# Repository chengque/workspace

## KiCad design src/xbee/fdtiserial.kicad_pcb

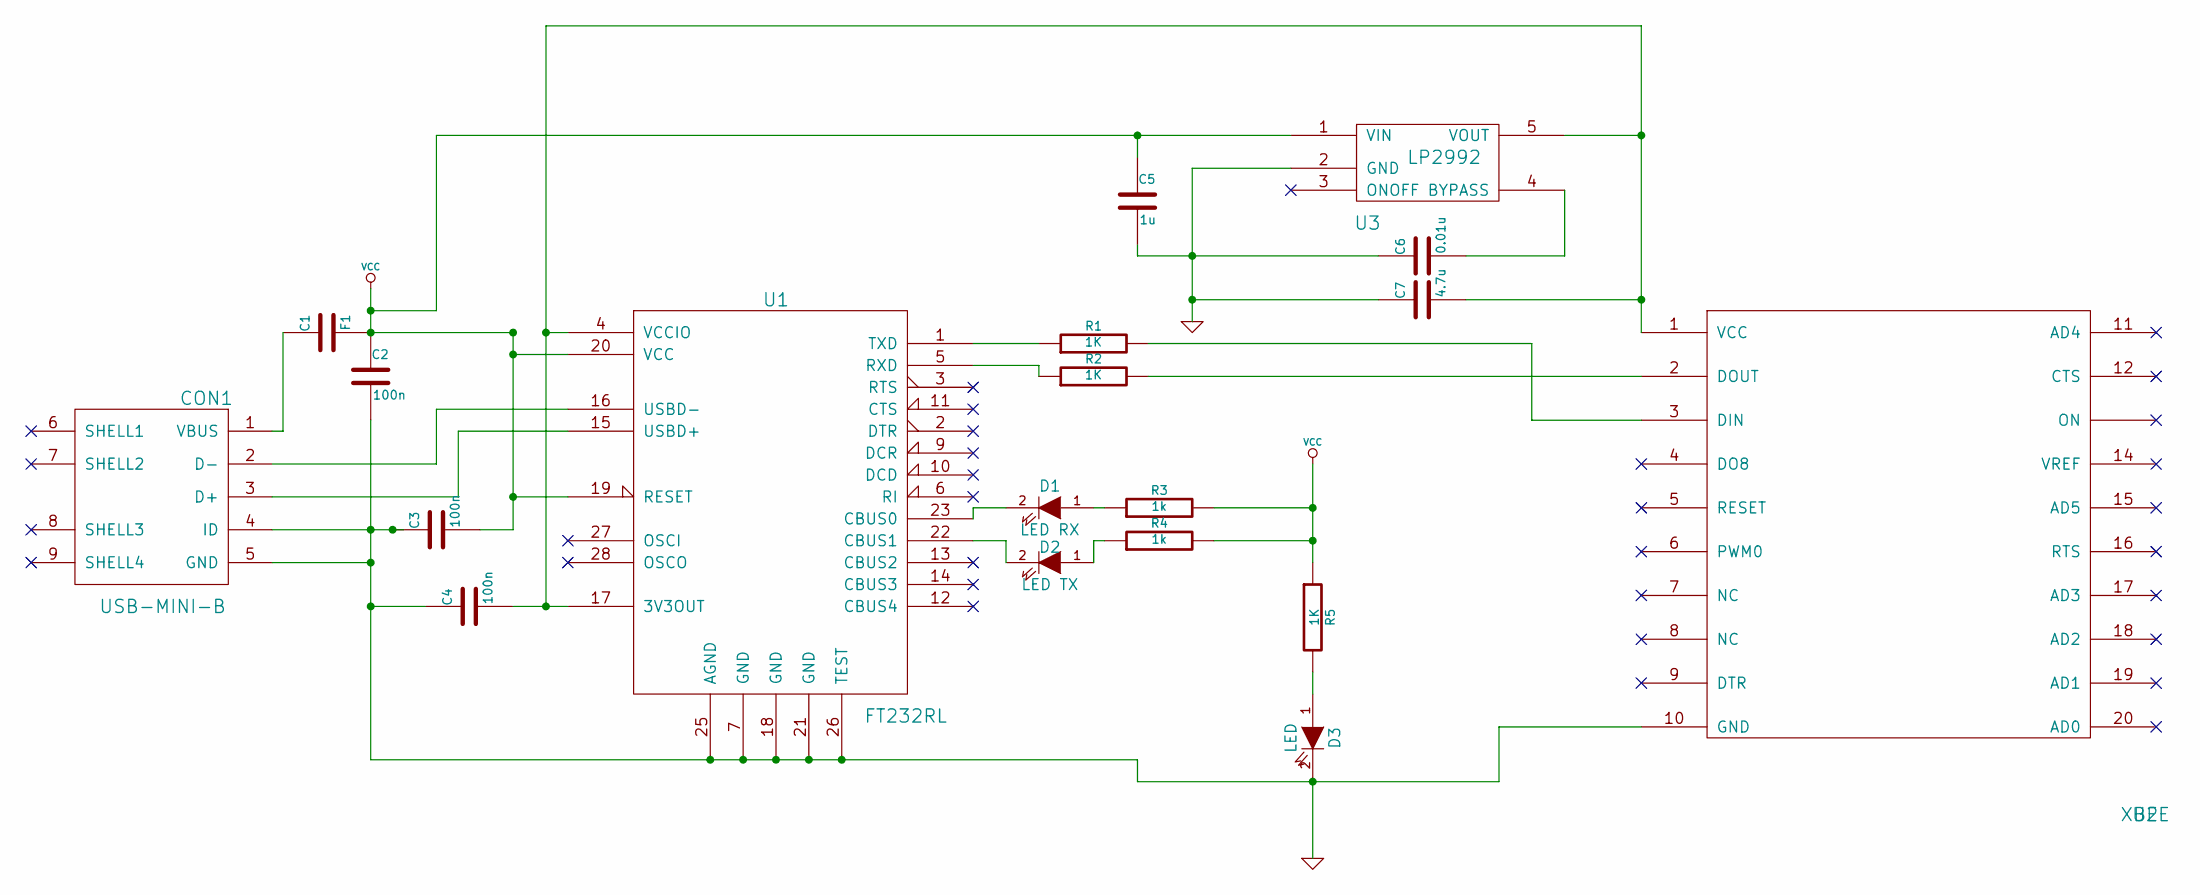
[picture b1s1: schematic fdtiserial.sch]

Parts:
C1: F1
C2, C3, C4: 100n
C5: 1u
C6: 0.01u
C7: 4.7u
CON1: USB-MINI-B
D1: LED RX
D2: LED TX
D3: LED
R1, R2, R5: 1K
R3, R4: 1k
U1: FT232RL
U2: XBEE
U3: LP2992

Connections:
GND: C2.2, C3.1, C4.1, C5.2, C6.1, C7.1, CON1.4 (ID), CON1.5 (GND), D3.2 (K), U1.7 (GND), U1.18 (GND), U1.21 (GND), U1.25 (AGND), U1.26 (TEST), U2.10 (GND), U3.2 (GND)
unnamed: C6.2, U3.4 (BYPASS)
unnamed: R2.2, U2.2 (DOUT)
unnamed: R1.2, U2.3 (DIN)
unnamed: CON1.3 (D+), U1.15 (USBD+)
unnamed: C1.1, CON1.1 (VBUS)
unnamed: CON1.2 (D-), U1.16 (USBD-)
unnamed: R2.1, U1.5 (RXD)
unnamed: D2.2 (K), U1.22 (CBUS1)
unnamed: D1.1 (A), R3.1
unnamed: D1.2 (K), U1.23 (CBUS0)
unnamed: D2.1 (A), R4.1
unnamed: D3.1 (A), R5.2
unnamed: C4.2, C7.2, U1.4 (VCCIO), U1.17 (3V3OUT), U2.1 (VCC), U3.5 (VOUT)
unnamed: R1.1, U1.1 (TXD)
VCC: C1.2, C2.1, C3.2, C5.1, R3.2, R4.2, R5.1, U1.19 (RESET), U1.20 (VCC), U3.1 (VIN)

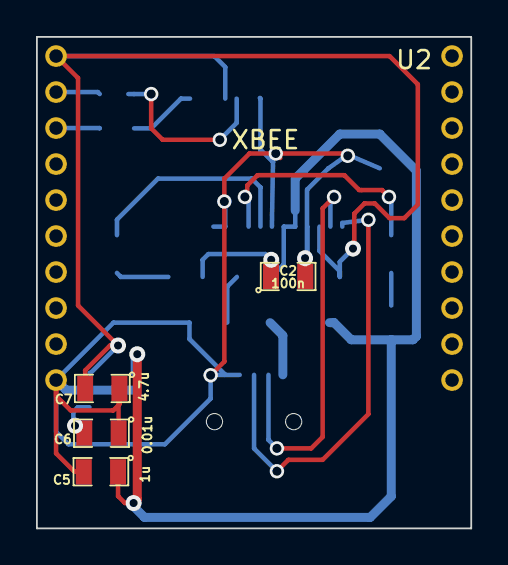
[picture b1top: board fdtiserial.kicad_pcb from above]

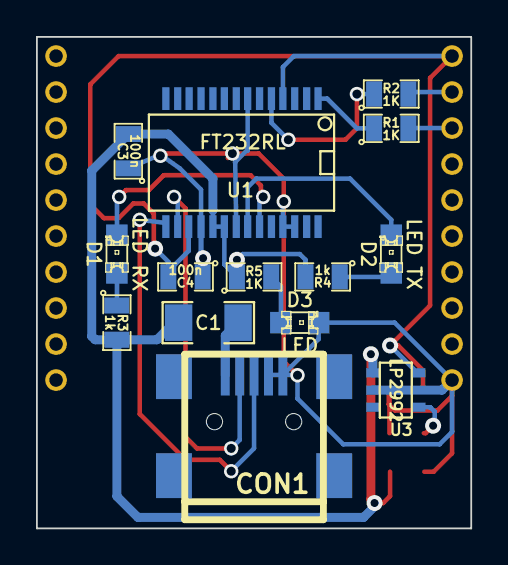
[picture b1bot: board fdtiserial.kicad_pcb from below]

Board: 2 copper layers, 24.1 x 27.3 mm, 19 parts (14 on the bottom side), 16 nets.

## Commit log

2015-06-04 development
2015-06-04 Firmware and Mavlink
2015-06-04 mavlink
2015-06-04 init
2015-06-04 Firmware
2015-06-04 Firmwawwwm
